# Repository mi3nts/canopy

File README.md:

# CANOPY Community Avian and AirQuality Network for Observing Pollution Year-round
Contains firmware for the Community Avian and AirQuality Network for Observing Pollution Year-round(CANOPY)

## Suggested Framework 

## 📋 Summary
This system design leverages an **Odroid** as a powerful Edge IoT node, integrating local data collection, processing, and resilient cloud synchronization. All local services and custom sensor readers are managed via **Git repositories** for version control and streamlined deployments. The system ensures continuous operation during internet outages by storing data locally and syncing to the cloud when connectivity is restored, while also publishing live data to the cloud via MQTT.

---

## 🚀 Components

- **Git-Managed Dockerized Sensor Readers**: Python containers pulled from Git, reading sensors and publishing data via MQTT.
- **Git-Managed Local Services**:
  - **Mosquitto (MQTT Broker)**: Manages local messaging.
  - **Node-RED**: Handles data routing, automation, and local storage to InfluxDB.
  - **InfluxDB (Local)**: Buffers time-series data at the edge.
  - **Telegraf**: Continuously syncs local InfluxDB data to Cloud InfluxDB.
  - **Grafana**: Provides edge visualization for real-time monitoring without relying on cloud access.
- **Cloud Backend**: Centralized Node-RED, InfluxDB, and Grafana for real-time processing, long-term storage, and visualization.

---

## 🌐 Data Flow
1. Sensors connected to Odroid are read by Dockerized Python sensor readers deployed from Git - The current repo.
2. Sensor data is published to:
   - **Local MQTT Broker** for edge processing.
   - **Cloud MQTT Broker** for real-time cloud ingestion.
3. Node-RED (Edge) subscribes to local MQTT, processes data, and stores it in local InfluxDB.
4. Telegraf syncs buffered data from local InfluxDB to Cloud InfluxDB.
5. Cloud Node-RED and Grafana handle advanced workflows and visualization.

---

## 🛡️ Key Features
- **Git-Managed Deployments**: Version control for all services and sensor readers.
- **Offline Resilience**: Full functionality without internet.
- **Live Data Streaming**: Real-time data published to cloud via MQTT.
- **Automated Cloud Sync**: Telegraf ensures data consistency between edge and cloud.
- **Modular & Scalable**: Docker-based deployment for easy management.
- **Flexible Automation**: Node-RED enables custom logic and integrations.

---

## 🚀 Deployment Steps
1. Clone Git repositories for local services and sensor readers.
2. Deploy Docker Compose stack on Odroid (MQTT, Node-RED, InfluxDB, Telegraf, Grafana).
3. Run sensor reader containers from Git.
4. Configure Node-RED flows for data handling.
5. Set up Telegraf for continuous cloud sync.
6. Deploy local Grafana for edge-based dashboards and visualization.
7. Access cloud Node-RED and Grafana for real-time monitoring and dashboards.

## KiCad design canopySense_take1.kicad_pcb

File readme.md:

# CANOPY Community Avian and AirQuality Network for Observing Pollution Year-round
Contains firmware for the Community Avian and AirQuality Network for Observing Pollution Year-round(CANOPY)

## Suggested Framework 

### 📋 Summary
This system design leverages an **Odroid** as a powerful Edge IoT node, integrating local data collection, processing, and resilient cloud synchronization. All local services and custom sensor readers are managed via **Git repositories** for version control and streamlined deployments. The system ensures continuous operation during internet outages by storing data locally and syncing to the cloud when connectivity is restored, while also publishing live data to the cloud via MQTT.

---

## Electrical Data Parts List
- **Raspberry Pi Zero 2W** (on [Dream V2.0 PCB Board](https://github.com/mi3nts/PCBMints2025) or later)
    - OPC-N3 
    - SJH-5A Methane Sensor (Not working on Dream V2.0 or earlier)
    - BME280 
    - IPS7100
    - COZIR AH-E-1
- **2x Odroid N2**
    - RS-FSXCS Anemometer
    - AS7265X
    - LTR390
    - SEN0463 Radiation sensor
    - 2x G-MOUSE USB GPS
    - USB Camera
    - USB Microphone
- **2x Arduino Boards**
    - One for managing the relays (receives input from odroidHeartbeat.py)
        - Ensure step up to 5V if board outputs 3.3V
    - One for digitalizing analog outputs from SEN0463

---

## Data Management
- **Git-Managed Dockerized Sensor Readers**: Python containers pulled from Git, reading sensors and publishing data via MQTT.
- **Git-Managed Local Services**:
  - **Mosquitto (MQTT Broker)**: Manages local messaging.
  - **Node-RED**: Handles data routing, automation, and local storage to InfluxDB.
  - **InfluxDB (Local)**: Buffers time-series data at the edge.
  - **Telegraf**: Continuously syncs local InfluxDB data to Cloud InfluxDB.
  - **Grafana**: Provides edge visualization for real-time monitoring without relying on cloud access.
- **Cloud Backend**: Centralized Node-RED, InfluxDB, and Grafana for real-time processing, long-term storage, and visualization.

---

### 🌐 Data Flow
1. Sensors connected to Odroid are read by Dockerized Python sensor readers deployed from Git - The current repo.
2. Sensor data is published to:
   - **Local MQTT Broker** for edge processing.
   - **Cloud MQTT Broker** for real-time cloud ingestion.
3. Node-RED (Edge) subscribes to local MQTT, processes data, and stores it in local InfluxDB.
4. Telegraf syncs buffered data from local InfluxDB to Cloud InfluxDB.
5. Cloud Node-RED and Grafana handle advanced workflows and visualization.

---

### 🛡️ Key Features
- **Git-Managed Deployments**: Version control for all services and sensor readers.
- **Offline Resilience**: Full functionality without internet.
- **Live Data Streaming**: Real-time data published to cloud via MQTT.
- **Automated Cloud Sync**: Telegraf ensures data consistency between edge and cloud.
- **Modular & Scalable**: Docker-based deployment for easy management.
- **Flexible Automation**: Node-RED enables custom logic and integrations.

---

## 🚀 Deployment Steps
1. Clone Git repositories for local services and sensor readers.
2. Deploy Docker Compose stack on Odroid (MQTT, Node-RED, InfluxDB, Telegraf, Grafana).
3. Run sensor reader containers from Git.
4. Configure Node-RED flows for data handling.
5. Set up Telegraf for continuous cloud sync.
6. Deploy local Grafana for edge-based dashboards and visualization.
7. Access cloud Node-RED and Grafana for real-time monitoring and dashboards.

### Odroid N2 Pinout Connection
- **Connection for 1B
-

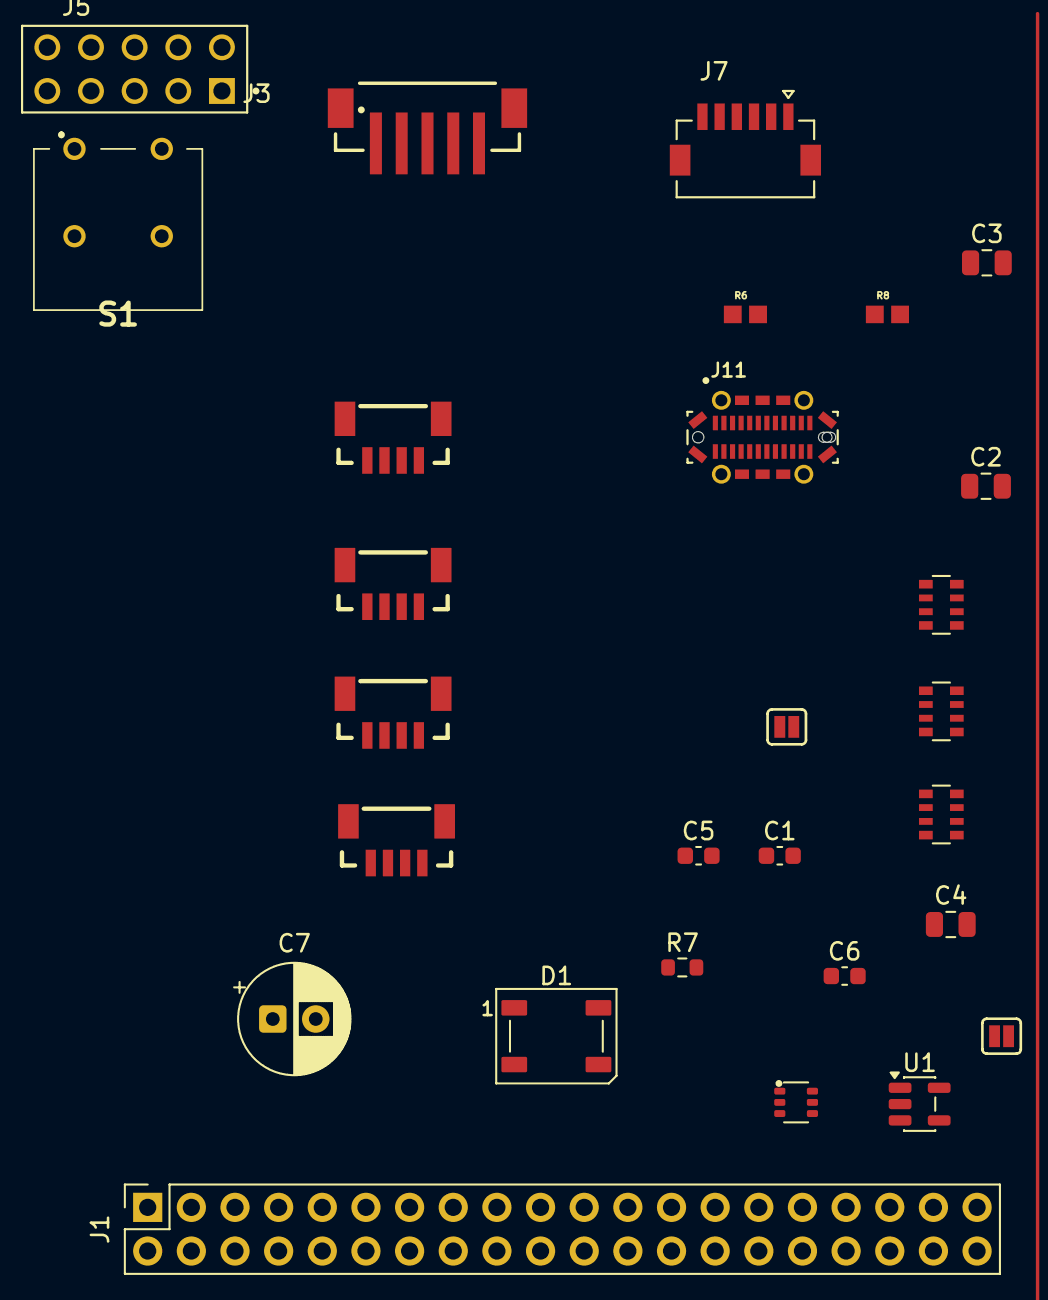
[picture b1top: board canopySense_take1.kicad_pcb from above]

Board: 2 copper layers, 28 parts (0 on the bottom side), 26 nets, no tracks yet.

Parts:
C1, C5, C6: 0.1uF; C_0603_1608Metric
C2, C3, C4: 10uF; C_0805_2012Metric
C7: EEV107M010S9GAA; CP_Radial_D6.3mm_P2.50mm
D1: WS2812B_5050; LED_WS2812B_PLCC4_5.0x5.0mm_P3.2mm
J1: GPIO; PinSocket_2x20_P2.54mm_Vertical
J2, J4, J6: Qwiic_Vertical; JST_1x04_P1.0mm_Vertical_SMD
J3: 679305124022
J5: M20-7830542; HARWIN_M20-7830542
J7: 5013310607; MOLEX_5013310607
J11: 10132328-10011LF; AMPHENOL_10132328-10011LF
JP2, JP3: Jumper_2_NO
Q1: BSS138; SOT-363
R1, R2, R5: 10k; R_Array_Convex_4x0603
R6: RC0603FR-075K1L; RESC1607X60N
R7: 5.1k; R_0603_1608Metric
R8: RC0603FR-07330RL; RESC1607X60N
S1: AB11AH-FC; AB11AHFC
U1: AP2112K-3.3; SOT-23-5
j9: Qwiic_Vertical; JST_1x04_P1.0mm_Vertical_SMD

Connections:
+3V3: C2.1, J1.1, J1.17, J2.2, J5.3, J6.2, R1.2, R1.4, U1.1 (VIN), U1.3 (EN), j9.2
+5V: C4.1, C5.1, C6.1, C7.P, D1.1 (VDD), J1.2, J1.4, J3.1, J4.2, J7.1, JP2.2 (B), JP3.2 (B), R5.2, R5.4, S1.3
/5V_BUS_USB: J11.A4 (VBUS_A4), J11.A9 (VBUS_A9), J11.B4 (VBUS_B4), J11.B9 (VBUS_B9), S1.1
/BME_SCL: Q1.1 (S), R1.5
/BME_SDA: Q1.4 (S), R1.8
/GPIO2/SDA1: J1.3, j9.3
/GPIO3/SCL1: J1.5, j9.4
/GPIO5/SDA5: J1.29, J2.3, Q1.3 (D), R1.3
/GPIO6/SCL5: J1.31, J2.4, Q1.6 (D), R1.1
/GPIO8/SPI0.CE0: J1.24, J7.5
/GPIO9/SPI0.MISO: J1.21, J7.3
/GPIO10/SPI0.MOSI: J1.19, J7.4
/GPIO11/SPI0.SCLK: J1.23, J7.2
/GPIO14/TXD0: J1.8, J5.5, J6.3
/GPIO15/RXD0: J1.10, J5.7, J6.4
/GPIO22/SCL3: J1.15, J3.3, J4.4
/GPIO23/SDA4: J1.16, R5.1
/GPIO24/SCL4: J1.18, R5.3
/GPIO27/SDA3: J1.13, J3.2, J4.3
/INA_ADD0: JP2.1 (A), R2.5
/INA_ADD1: JP3.1 (A), R2.8
BME_3V3: C1.1, C3.1, Q1.2 (G), Q1.5 (G), R1.6, R1.7, U1.5 (VOUT)
GND: C1.2, C2.2, C3.2, C4.2, C5.2, C6.2, C7.N, D1.3 (VSS), J1.6, J1.9, J1.14, J1.20, J1.25, J1.30, J1.34, J1.39, J2.1, J3.4, J3.5, J4.1, J5.1, J5.4, J5.6, J6.1, J7.6, J11.1 (SHIELD), J11.2 (SHIELD__1), J11.3 (SHIELD__2), J11.4 (SHIELD__3), J11.5 (SHIELD__4), J11.6 (SHIELD__5), J11.7 (SHIELD__6), J11.8 (SHIELD__7), J11.9 (SHIELD__8), J11.10 (SHIELD__9), J11.11 (SHIELD__10), J11.12 (SHIELD__11), J11.13 (SHIELD__12), J11.14 (SHIELD__13), J11.A1 (GND_A1), J11.A12 (GND_A12), J11.B1 (GND_B1), J11.B12 (GND_B12), R2.6, R2.7, R6.1, R7.1, U1.2 (GND), j9.1
unnamed: D1.4 (DIN), R8.1
unnamed: J11.A5 (CC1), R7.2
unnamed: J11.B5 (CC2), R6.2

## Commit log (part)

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2025-04-21 modified: README.md
2025-04-21 Added CanopyNetworkDiagram.drawio
2025-04-21 Added CanopyNetworkDiagram.drawio.png
2025-04-23 Updated Names
2025-04-24 Rename README.md to readme.md
2025-04-24 Rename LICENSE to licence
2025-04-24 Rename licence to license
2025-11-17 added initial opc reader python file
2025-12-15 Initial KiCad project
2025-12-17 Initial backup archive of canopySense_take1
2025-12-20 Organize live KiCad project and archive ZIP backups
2026-02-12 added anemometer and opc firmware
2026-02-12 added mSR.sensorFinisher to opcReader
2026-02-12 added gpsReader.py, sen0463Reader.py, restructuring sub-board scripts to pcbFirmware
2026-02-12 minor improvements
2026-02-12 added arduino sketch/library
2026-02-12 fixed sen0463Reader.py
2026-02-13 add mints libraries
2026-02-15 Added full relay firmware
2026-02-15 Added notes to relayControl
2026-02-17 Update pinout diagram image reference in README
2026-02-19 fixed relayControl; added pcbFirmware/helper libraries
2026-02-23 updated libraries
2026-02-23 fixed findUSBGPSPort()
2026-02-23 trying to fix libraries :(
2026-02-26 bug fixes
2026-02-26 Fixed opc tag
2026-02-26 fixed import issues
2026-02-26 added missing functions to mSR
2026-02-26 runAll PCB
2026-03-02 added as7265x.py
2026-03-02 fixed keys formatting
2026-03-02 testing new opcReader.py
2026-03-05 fixed ozone libraries
2026-03-05 Fixed bugs and added find device by serial id
2026-03-05 added find device by serial id
2026-03-05 included audio recorder/analyzer
2026-03-05 included mintsAudio library
2026-03-05 newer audio files
2026-03-05 newer mintsAudio library
2026-03-05 mD fix
2026-03-05 sen0463 found by id
2026-03-08 runALlAudio script
2026-03-09 fixed audioReader finally
2026-03-09 basic ltr reader
2026-03-09 update runAll
2026-03-10 fixed opcReader to include proper fields
2026-03-10 added cloud tracking
2026-03-10 removed old files
2026-03-10 fixed skyCamReader upload
2026-03-10 update cronjob
2026-03-22 updated bird calls to dynamically find mic
2026-03-22 fixed fatal audio bug, made function camelCase, more Pythonic
2026-06-08 test ML
2026-06-09 almost working ips7100mc topic
2026-06-09 update ips7100Reader
2026-06-10 working local ips7100MC topic
